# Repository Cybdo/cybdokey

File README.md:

# CybdoKey
A RP2354 based usb hardware authentication key, or anything else you can write firmware for ;)

Cybdokey was made because yubikeys are too expensive and all the other options, including picofido on other devboards, were clunky. the user interaction button was tiny and hard to press, and depending on the board it was too big and/or needed an extra cable. Cybdokey was made to be a polished, compact FIDO key with capacative touch support.

**Note:** `bom.csv` is the LCSC parts list with working liks, whilst `overall-bom.csv` is an estimate of the overall project cost

## Zine Page / Poster

pdf in `assets/zine/Zine page.pdf`

## Features
- RP2354-based development board
- Stacked 2MB flash storage
- onboard USB-A connector
- Capacative touch pad with shine-through red and blue LEDs
- exposed 3V3, GND, RESET and BOOTSEL
- 2 keyring/accessory mount holes
- Hand-solderable (in theory)
- tiny form factor!

## Usage

Simply plug Cybdokey into your computer's USB-A port, and it will function similar to a yubikey. Passkeys and OTPs can be stored on it, and it supports human presence detection using the capacative touch pad. LED signals are identical to that of any other pico-fido key.

## Schematics

## PCB

|Front|Back|
|---|---|
| | |

## Firmware

See [https://github.com/cybdo/cybdokey-fw](https://github.com/cybdo/cybdokey-fw) for FIDO key firmware.

Firmware can be flashed on first boot, or by shorting the BOOTSEL jumper on the left side of the crystal, diagonally underneath the MCU, before booting.

CybdoKey is also compatiable with anything written for a RP2350/RP2354.

## Credits and Acknowledgements

 - [KiCad](https://www.kicad.org)
 - [Hack Club Fallout](https://fallout.hackclub.com)
 - [pcb2blender](https://github.com/30350n/pcb2blender)
 - [Blender](https://blender.org)
 - [MicroKey](https://github.com/Badbird5907/microkey)
 - [Pico FIDO](https://github.com/polhenarejos/pico-fido), forked to make [CybdoKey firmware](https://github.com/cybdo/cybdokey-fw)

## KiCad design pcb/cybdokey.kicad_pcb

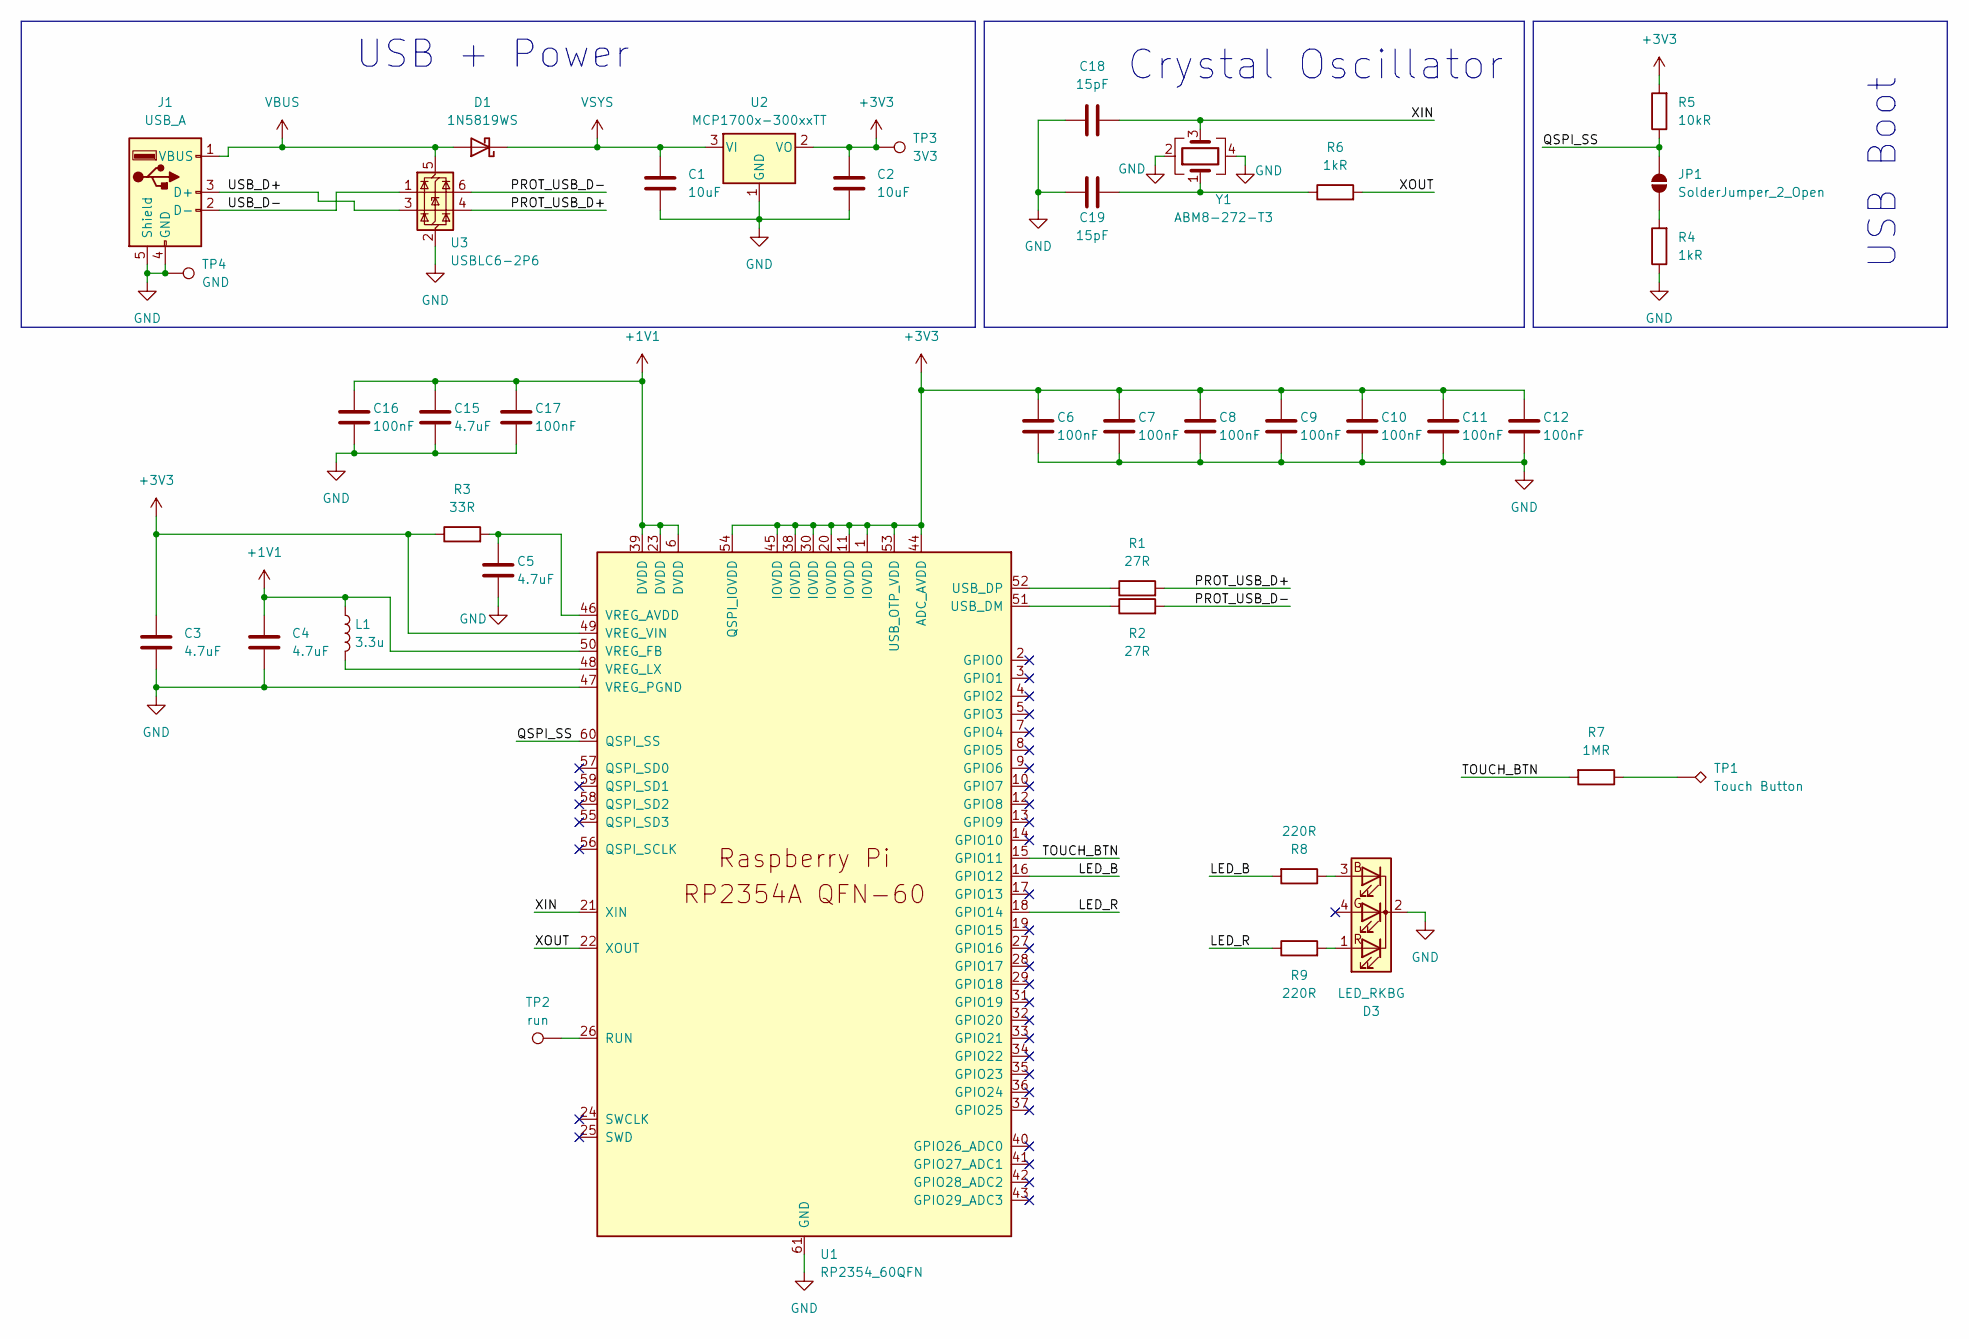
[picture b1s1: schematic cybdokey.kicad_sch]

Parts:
C1, C2: 10uF; C_0402_1005Metric_Pad0.74x0.62mm_HandSolder
C3, C4, C5, C15: 4.7uF; C_0402_1005Metric_Pad0.74x0.62mm_HandSolder
C6, C7, C8, C9, C10, C11, C12, C16, C17: 100nF; C_0402_1005Metric_Pad0.74x0.62mm_HandSolder
C18, C19: 15pF; C_0402_1005Metric_Pad0.74x0.62mm_HandSolder
D1: 1N5819WS; D_SOD-323F
D3: LED_RKBG; LED-SMD_4P-L3.2-W2.8_XZMDKCBDDG45S-9
J1: USB_A; USB_A_PCB_Edge_receptacle
JP1: SolderJumper_2_Open; SolderJumper-2_P1.3mm_Open_TrianglePad1.0x1.5mm
L1: 3.3u; INDC1608X95N
R1, R2: 27R; R_0402_1005Metric_Pad0.72x0.64mm_HandSolder
R3: 33R; R_0402_1005Metric_Pad0.72x0.64mm_HandSolder
R4, R6: 1kR; R_0402_1005Metric_Pad0.72x0.64mm_HandSolder
R5: 10kR; R_0402_1005Metric_Pad0.72x0.64mm_HandSolder
R7: 1MR; R_0402_1005Metric_Pad0.72x0.64mm_HandSolder
R8, R9: 220R; R_0402_1005Metric_Pad0.72x0.64mm_HandSolder
TP1: Touch Button; touchpad
TP2: run; TestPoint_Pad_1.0x1.0mm
TP3: 3V3; TestPoint_Pad_1.0x1.0mm
TP4: GND; TestPoint_Pad_1.0x1.0mm
U1: RP2354_60QFN; RP2350-QFN-60-1EP_7x7_P0.4mm_EP3.4x3.4mm_ThermalVias
U2: MCP1700x-300xxTT; SOT-23
U3: USBLC6-2P6; SOT-666
Y1: ABM8-272-T3; Crystal_SMD_Abracon_ABM8G-4Pin_3.2x2.5mm

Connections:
+1V1: C4.1, C15.1, C16.1, C17.1, L1.1, U1.6 (DVDD), U1.23 (DVDD), U1.39 (DVDD), U1.50 (VREG_FB)
+3V3: C2.1, C3.1, C6.1, C7.1, C8.1, C9.1, C10.1, C11.1, C12.1, R3.1, R5.2, TP3.1, U1.1 (IOVDD), U1.11 (IOVDD), U1.20 (IOVDD), U1.30 (IOVDD), U1.38 (IOVDD), U1.44 (ADC_AVDD), U1.45 (IOVDD), U1.49 (VREG_VIN), U1.53 (USB_OTP_VDD), U1.54 (QSPI_IOVDD), U2.2 (VO)
/LED_B: R8.2, U1.16 (GPIO12)
/LED_R: R9.1, U1.18 (GPIO14)
/PROT_USB_D+: R1.2, U3.4 (I/O2)
/PROT_USB_D-: R2.2, U3.6 (I/O1)
/QSPI_SS: JP1.2 (B), R5.1, U1.60 (QSPI_SS)
/TOUCH_BTN: R7.2, U1.15 (GPIO11)
/USB_D+: J1.3 (D+), U3.3 (I/O2)
/USB_D-: J1.2 (D-), U3.1 (I/O1)
/XIN: C18.2, U1.21 (XIN), Y1.3
/XOUT: R6.2, U1.22 (XOUT)
GND: C1.2, C2.2, C3.2, C4.2, C5.2, C6.2, C7.2, C8.2, C9.2, C10.2, C11.2, C12.2, C15.2, C16.2, C17.2, C18.1, C19.2, D3.2 (K), J1.4 (GND), J1.5 (Shield), R4.1, TP4.1, U1.47 (VREG_PGND), U1.61 (GND), U2.1 (GND), U3.2 (GND), Y1.2, Y1.4
unnamed: C19.1, R6.1, Y1.1
unnamed: D3.3 (BA), R8.1
unnamed: D3.1 (RA), R9.2
unnamed: JP1.1 (A), R4.2
unnamed: R7.1, TP1.1
unnamed: TP2.1, U1.26 (RUN)
unnamed: R2.1, U1.51 (USB_DM)
unnamed: R1.1, U1.52 (USB_DP)
unnamed: C5.1, R3.2, U1.46 (VREG_AVDD)
unnamed: L1.2, U1.48 (VREG_LX)
VBUS: D1.2 (A), J1.1 (VBUS), U3.5 (VBUS)
VSYS: C1.1, D1.1 (K), U2.3 (VI)

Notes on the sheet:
Crystal Oscillator
USB Boot
USB + Power

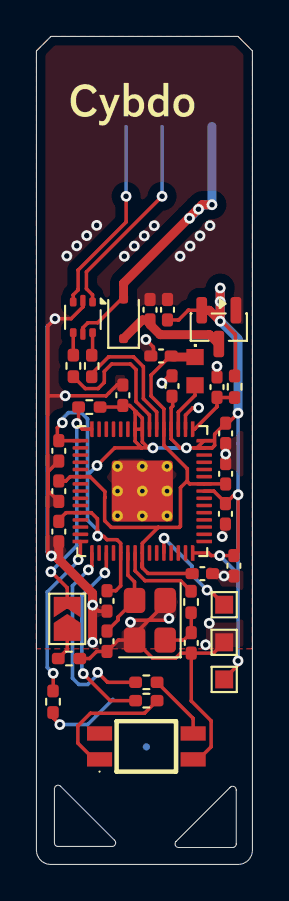
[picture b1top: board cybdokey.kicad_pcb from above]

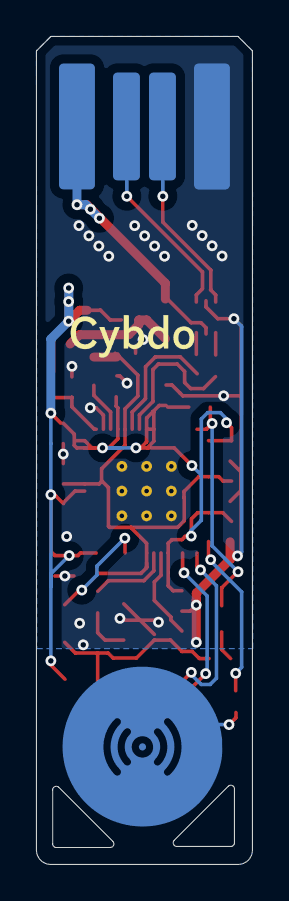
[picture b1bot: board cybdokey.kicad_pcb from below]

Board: 2 copper layers, 12.0 x 46.0 mm, 39 parts (2 on the bottom side), 25 nets.

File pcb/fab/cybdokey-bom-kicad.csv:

"Id","Designator","Footprint","Quantity","Designation","Supplier and ref",
1,"C7,C6,C8,C16,C12,C10,C17,C11,C9","C_0402_1005Metric_Pad0.74x0.62mm_HandSolder",9,"100nF",,,
2,"D1","D_SOD-323F",1,"1N5819WS",,,
3,"R6,R4","R_0402_1005Metric_Pad0.72x0.64mm_HandSolder",2,"1kR",,,
4,"C18,C19,C5,C3,C4,C15","C_0402_1005Metric_Pad0.74x0.62mm_HandSolder",6,"4.7uF",,,
5,"R2,R1","R_0402_1005Metric_Pad0.72x0.64mm_HandSolder",2,"27R",,,
6,"R7","R_0402_1005Metric_Pad0.72x0.64mm_HandSolder",1,"1MR",,,
7,"R3","R_0402_1005Metric_Pad0.72x0.64mm_HandSolder",1,"33R",,,
8,"TP2","TestPoint_Pad_1.0x1.0mm",1,"run",,,
9,"C2,C1","C_0402_1005Metric_Pad0.74x0.62mm_HandSolder",2,"10uF",,,
10,"Y1","Crystal_SMD_Abracon_ABM8G-4Pin_3.2x2.5mm",1,"ABM8-272-T3",,,
11,"R5","R_0402_1005Metric_Pad0.72x0.64mm_HandSolder",1,"10kR",,,
12,"D3","LED-SMD_4P-L3.2-W2.8_XZMDKCBDDG45S-9",1,"LED_RKBG",,,
13,"TP4","TestPoint_Pad_1.0x1.0mm",1,"GND",,,
14,"U1","RP2350-QFN-60-1EP_7x7_P0.4mm_EP3.4x3.4mm_ThermalVias",1,"RP2354_60QFN",,,
15,"TP3","TestPoint_Pad_1.0x1.0mm",1,"3V3",,,
16,"L1","INDC1608X95N",1,"3.3u",,,
17,"U3","SOT-666",1,"USBLC6-2P6",,,
18,"R9,R8","R_0402_1005Metric_Pad0.72x0.64mm_HandSolder",2,"220R",,,
19,"U2","SOT-23",1,"MCP1700x-300xxTT",,,
20,"J1","USB_A_PCB_Edge_receptacle",1,"USB_A",,,
21,"REF**","cybdokey",1,"cybdokey",,,

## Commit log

2026-04-04 finished schematics
2026-04-04 started routing
2026-04-05 more routing
2026-04-05 routing done... for now
2026-04-07 cleaned up routing
2026-04-07 cleaned up routing the second
2026-04-17 changed LED, moving back to windows
2026-04-18 add new touch button footprint and add some branding
2026-04-18 add cybdokey branding
    i forgor
2026-04-19 polishing, started with some renders
2026-04-19 Revise README with project details and features
    Updated project name and added detailed features section.
2026-04-21 render stuff, add zine page
2026-04-21 add zine page to readme
2026-04-21 make production files, add bom
2026-04-21 csvs were gitignored oops
2026-04-22 fix zine page, fix touchpad shinethrouhg window area
2026-04-23 Add external repository as submodule
2026-04-23 Update submodule URL for firmware
2026-04-23 redo submodule
2026-04-23 Rename bom.csv to overall-bom.csv
2026-04-23 Rename lcsc-bom.csv to bom.csv
